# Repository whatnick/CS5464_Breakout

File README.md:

# CS5464 Cirrus Logic AC-Energy Monitor Breakout

Minimal breakout board to test and develop drivers for the Cirrus Logic CS5464 Single-phase Energy Monitor ASIC.

Arduino code available [here](https://github.com/whatnick/CS5464_Arduino)

Features include:
- RC networks for sampling Voltage and Current.
- Crystal to provide clock to ASIC.

# Board Plots

## Board Front

## Board Back

## 3D Render

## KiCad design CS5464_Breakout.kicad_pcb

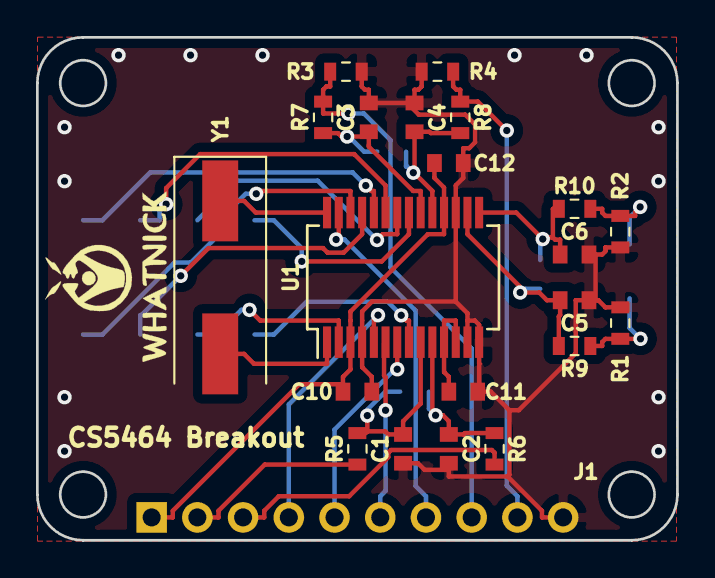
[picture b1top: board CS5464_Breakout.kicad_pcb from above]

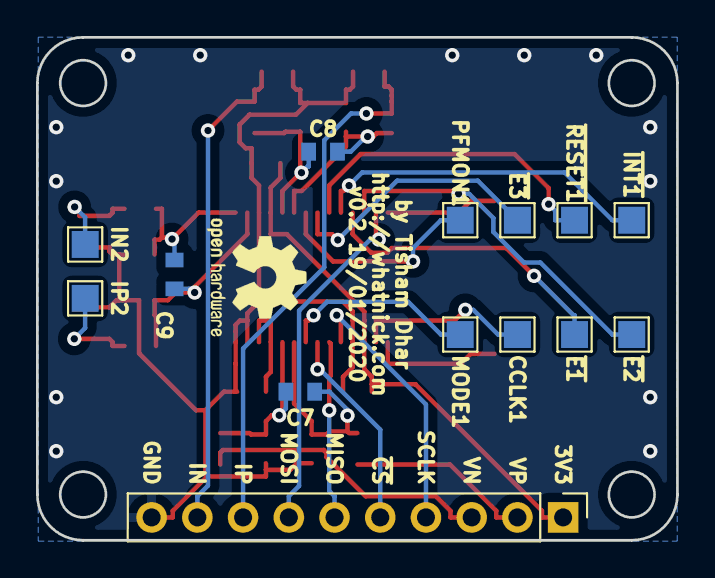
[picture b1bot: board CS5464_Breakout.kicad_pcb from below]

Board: 2 copper layers, 35.6 x 27.9 mm, 32 parts (10 on the bottom side), 24 nets.

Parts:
C1, C2, C3, C4, C5, C6: 27nF; C_0603_1608Metric
C7, C8, C9: C_Small; C_0603_1608Metric
C10, C11, C12: 100nF; C_0603_1608Metric
CCLK1: CPUCLK; TestPoint_Pad_1.5x1.5mm
G1: LOGO; Whatnick_logo
IN2: IN2; TestPoint_Pad_1.5x1.5mm
IP2: IP2; TestPoint_Pad_1.5x1.5mm
J1: Conn_01x10; PinHeader_1x10_P2.54mm_Vertical
LOGO1: Logo_Open_Hardware_Small; OSHW-Logo2_7.3x6mm_SilkScreen
MODE1: MODE; TestPoint_Pad_1.5x1.5mm
PFMON1: PFMON; TestPoint_Pad_1.5x1.5mm
R1, R2, R3, R4: 2.4R; R_0603_1608Metric
R5, R6, R7, R8, R9, R10: 1K; R_0603_1608Metric
U1: CS5464-ISZ; SSOP-28_5.3x10.2mm_P0.65mm
Y1: 4.096MHz; Crystal_SMD_HC49-SD

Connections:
+3V3: C10.1, C12.1, J1.1, U1.3, U1.18
GND: C1.2, C2.1, C3.2, C4.1, C5.2, C6.1, C10.2, C11.1, C12.2, J1.10, R1.1, R2.2, R3.1, R4.2, U1.4, U1.13, U1.14, U1.17
IIN1+: C3.1, C8.1, R7.1, U1.20
IIN1-: C4.2, C8.2, R8.1, U1.19
IIN2+: C5.1, C9.1, R9.1, U1.16
IIN2-: C6.2, C9.2, R10.1, U1.15
IN: J1.9, R4.1, R8.2
IN2: IN2.1, R2.1, R10.2
IP: J1.8, R3.2, R7.2
IP2: IP2.1, R1.2, R9.2
MISO: J1.6, U1.6
MOSI: J1.7, U1.27
unnamed: CCLK1.1, U1.2
unnamed: MODE1.1, U1.8
unnamed: PFMON1.1, U1.21
unnamed: U1.1, Y1.2
unnamed: U1.28, Y1.1
SCLK: J1.4, U1.5
VIN+: C1.1, C7.1, R5.1, U1.9
VIN-: C2.2, C7.2, R6.1, U1.10
VN: J1.3, R6.2
VP: J1.2, R5.2
VREF: C11.2, U1.11, U1.12
~CS: J1.5, U1.7

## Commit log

2018-12-27 Initial import
2018-12-28 Add logos and part placement
2018-12-28 Add top render
2019-01-03 Update schematic and PCB
2019-01-06 Complete place and route and generate Gerbers
2019-01-07 Add DNP for pads and optional caps
2019-02-03 Add part numbers
2019-12-21 Add readme and BOM
2019-12-21 Fix grammar in README
2019-12-22 Add crystal 3D model
2019-12-22 Add plots via kicadScripts
2019-12-22 Add readme details and changelog
2019-12-22 Simplify BOM
2020-01-19 Add silk screen and shorted test pad name, bump version
2020-02-01 Add PCB images
